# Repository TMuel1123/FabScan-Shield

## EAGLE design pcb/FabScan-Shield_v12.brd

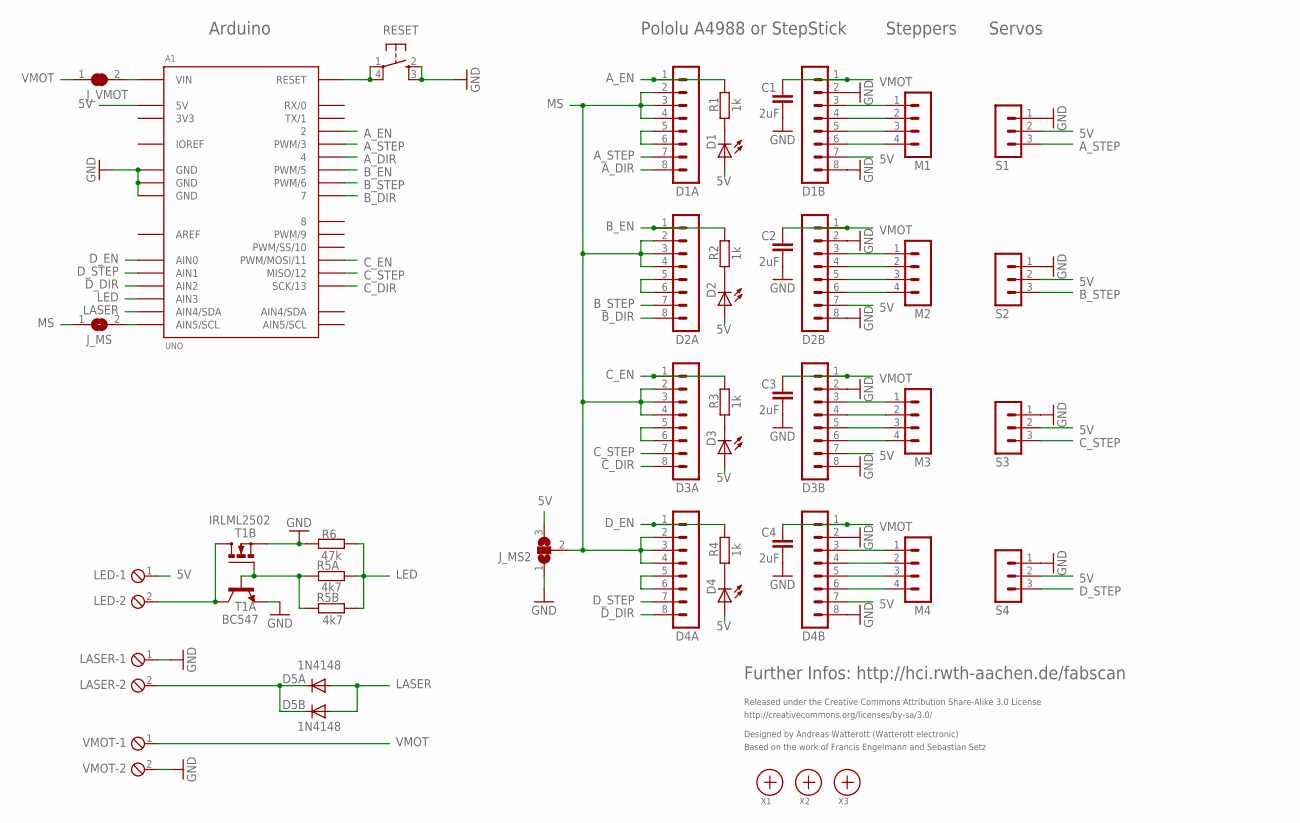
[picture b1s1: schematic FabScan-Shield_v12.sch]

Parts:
A1: UNO
C1, C2, C3, C4: 2uF; C0603
D1, D2, D3, D4: LEDCHIPLED_0603; CHIPLED_0603
D1A, D1B, D2A, D2B, D3A, D3B, D4A, D4B: MA08-1
D5A: 1N4148; DO35-7
D5B: 1N4148; SOD106-R
J_MS: SJ
J_MS2: SJ2W; SJ_2
J_VMOT: SJ
LASER: MPT2; 2POL254
LED: MPT2; 2POL254
M1, M2, M3, M4: MA04-1
R1, R2, R3, R4: 1k; R0603
R5A: 4k7; 0204/7
R5B: 4k7; R0603
R6: 47k; R0603
RESET: SW_SMDS; SW_SMD4
S1, S2, S3, S4: MA03-1
T1A: BC547; TO92
T1B: IRLML2502; MICRO3
VMOT: MPT2; 2POL254
X1, X2, X3: PASSER

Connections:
3V3: A1.3V3
5V: A1.5V, D1.A, D1B.7, D2.A, D2B.7, D3.A, D3B.7, D4.A, D4B.7, J_MS2.3, LED.1, S1.2, S2.2, S3.2, S4.2
AREF: A1.AREF
A_1A: D1B.5, M1.3
A_1B: D1B.6, M1.4
A_2A: D1B.4, M1.2
A_2B: D1B.3, M1.1
A_DIR: A1.4, D1A.8
A_EN: A1.2, D1A.1, R1.1
A_RST: D1A.5, D1A.6
A_STEP: A1.3 (PWM/3), D1A.7, S1.3
B_1A: D2B.5, M2.3
B_1B: D2B.6, M2.4
B_2A: D2B.4, M2.2
B_2B: D2B.3, M2.1
B_DIR: A1.7, D2A.8
B_EN: A1.5 (PWM/5), D2A.1, R2.1
B_STEP: A1.6 (PWM/6), D2A.7, S2.3
C_1A: D3B.5, M3.3
C_1B: D3B.6, M3.4
C_2A: D3B.4, M3.2
C_2B: D3B.3, M3.1
C_DIR: A1.13 (SCK/13), D3A.8
C_EN: A1.11 (PWM/MOSI/11), D3A.1, R3.1
C_STEP: A1.12 (MISO/12), D3A.7, S3.3
D_1A: D4B.5, M4.3
D_1B: D4B.6, M4.4
D_2A: D4B.4, M4.2
D_2B: D4B.3, M4.1
D_DIR: A1.AIN2, D4A.8
D_EN: A1.AIN0, D4A.1, R4.1
D_STEP: A1.AIN1, D4A.7, S4.3
GND: A1.GND@1 (GND), A1.GND@2 (GND), A1.GND@3 (GND), C1.2, C2.2, C3.2, C4.2, D1B.2, D1B.8, D2B.2, D2B.8, D3B.2, D3B.8, D4B.2, D4B.8, J_MS2.1, LASER.1, R6.2, RESET.2 (S), RESET.3 (S1), S1.1, S2.1, S3.1, S4.1, T1A.1 (E), T1B.2 (S), VMOT.2
IOREF: A1.IOREF
LASER: A1.AIN4 (AIN4/SDA), D5A.A, D5B.A
LED: A1.AIN3, R5A.1, R5B.2, R6.1
MS: D1A.2, D1A.3, D1A.4, D2A.2, D2A.3, D2A.4, D3A.2, D3A.3, D3A.4, D4A.2, D4A.3, D4A.4, J_MS.1, J_MS2.2
unnamed: D5A.C, D5B.C, LASER.2
unnamed: D1.C, R1.2
unnamed: D2.C, R2.2
unnamed: D3.C, R3.2
unnamed: D4A.5, D4A.6
unnamed: LED.2, T1A.3 (C), T1B.3 (D)
unnamed: D4.C, R4.2
unnamed: R5A.2, R5B.1, T1A.2 (B), T1B.1 (G)
unnamed: A1.AIN5 (AIN5/SCL), J_MS.2
unnamed: D2A.5, D2A.6
unnamed: D3A.5, D3A.6
RST: A1.RST (RESET), RESET.1, RESET.4 (P1)
VIN: A1.VIN, J_VMOT.2
VMOT: C1.1, C2.1, C3.1, C4.1, D1B.1, D2B.1, D3B.1, D4B.1, J_VMOT.1, VMOT.1

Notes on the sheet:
Released under the Creative Commons Attribution Share-Alike 3.0 License
http://creativecommons.org/licenses/by-sa/3.0/
Designed by Andreas Watterott (Watterott electronic)
Further Infos: http://hci.rwth-aachen.de/fabscan
Based on the work of Francis Engelmann and Sebastian Setz
Servos
Steppers
Arduino
Pololu A4988 or StepStick

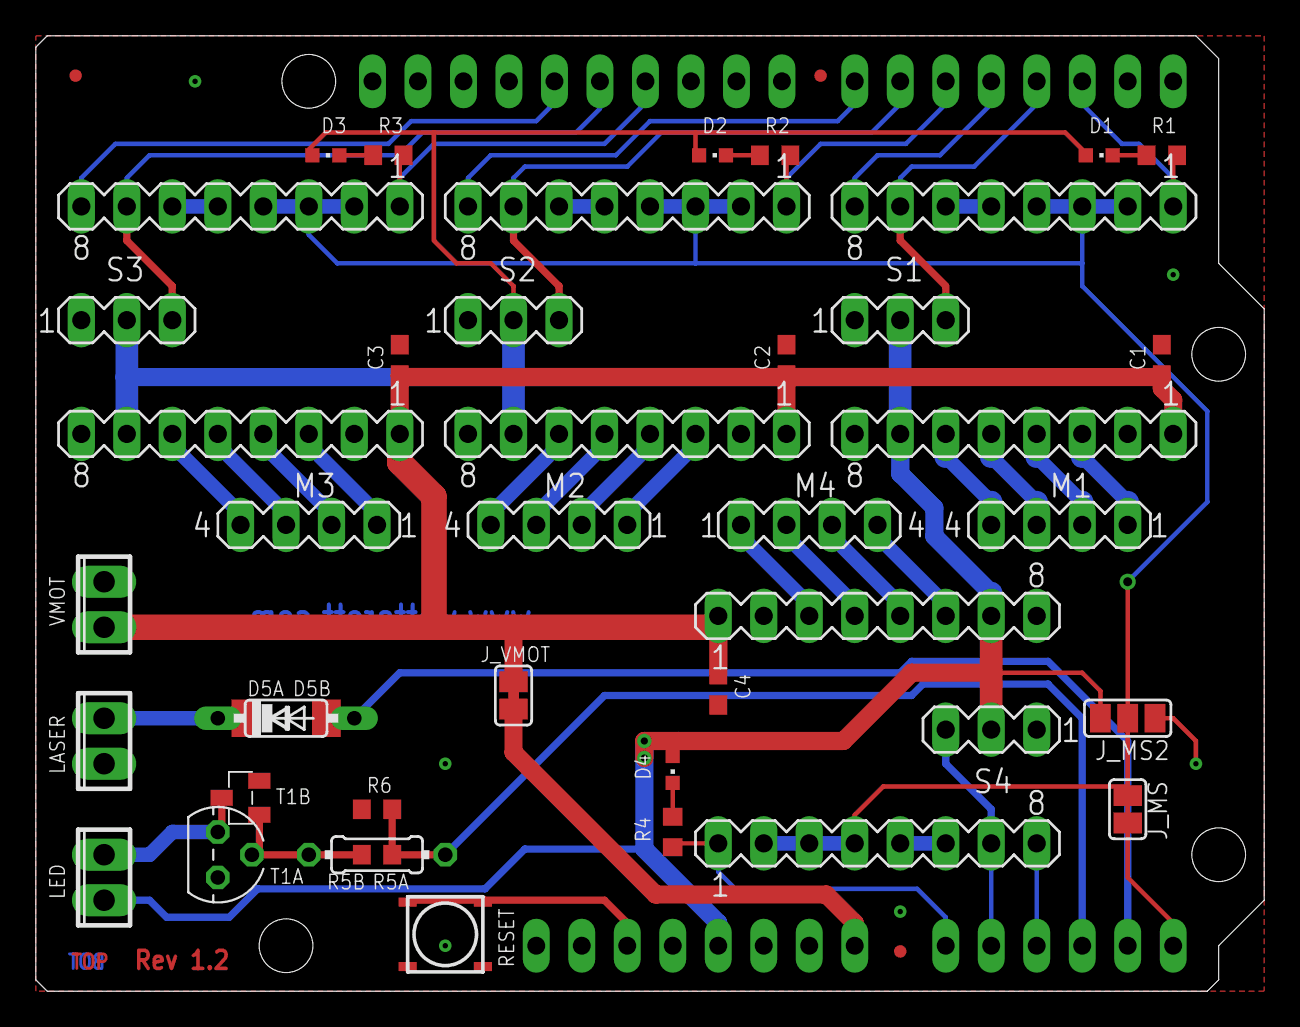
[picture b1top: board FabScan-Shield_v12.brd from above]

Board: 2 copper layers, 68.6 x 53.3 mm, 46 parts (0 on the bottom side), 48 nets.

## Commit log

2013-09-08 Minor change. Added a solder jumper to enable/disable the microstepping feature. This brings the nenefit that the SDA and SCL pins of the srduino can be used for I2C communication. TMuel
